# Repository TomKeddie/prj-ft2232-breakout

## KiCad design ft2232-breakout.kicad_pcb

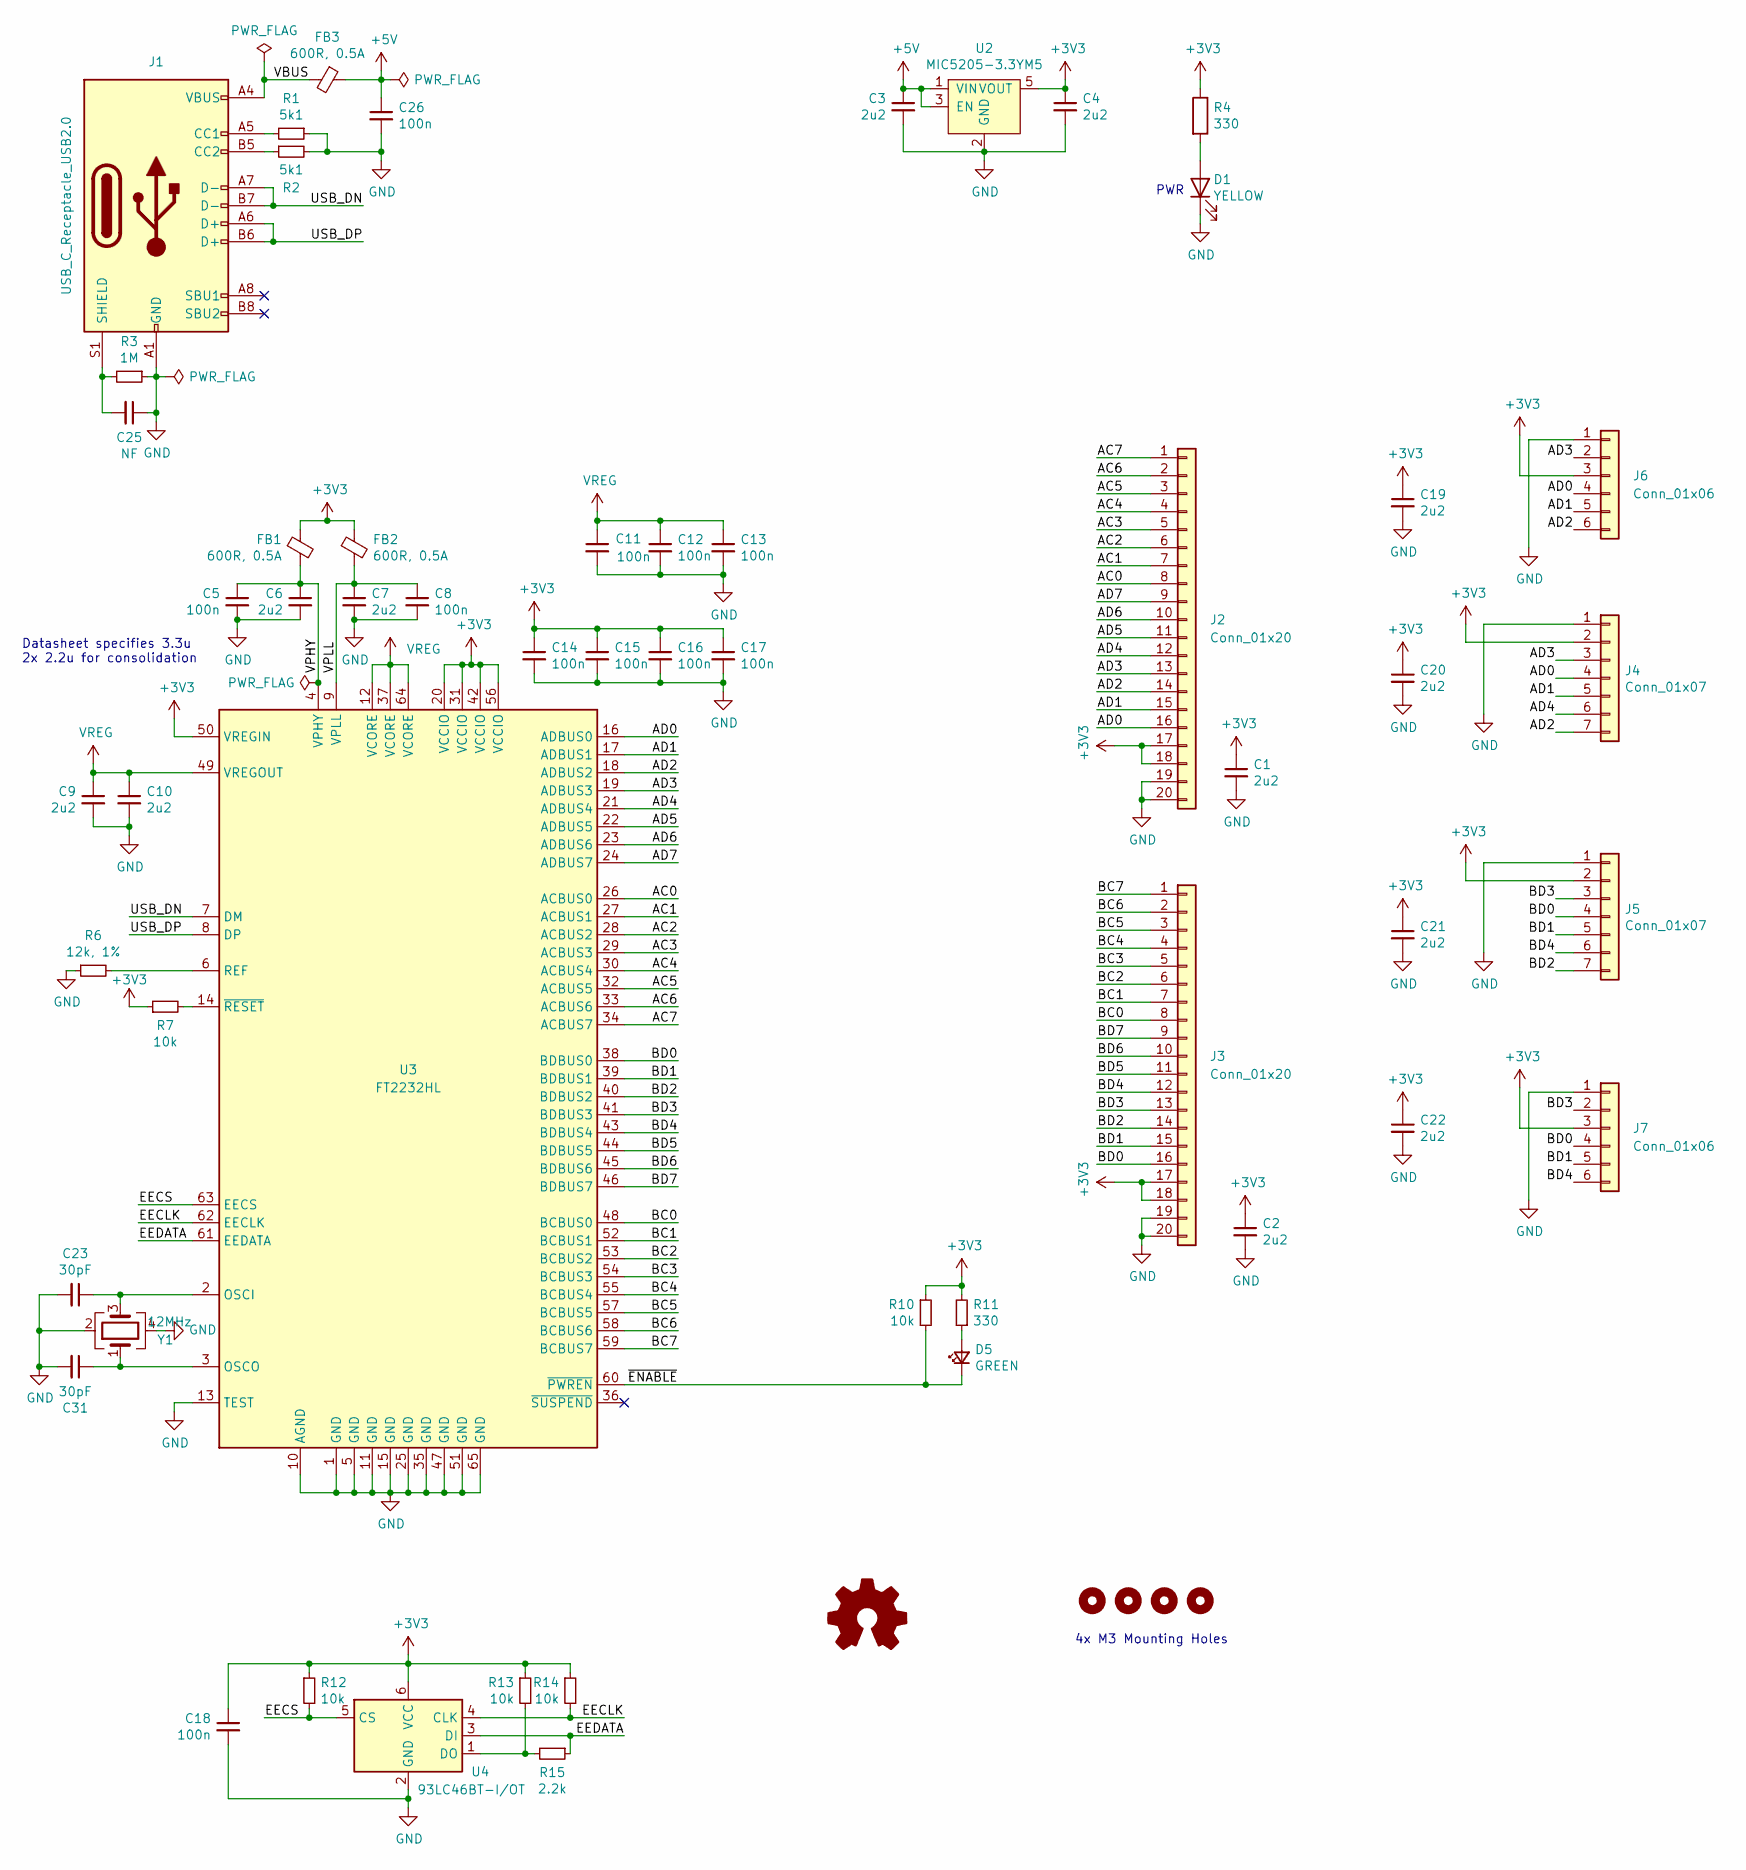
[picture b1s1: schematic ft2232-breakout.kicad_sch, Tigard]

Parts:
C1, C2, C3, C4, C6, C7, C9, C10, C19, C20, C21, C22: 2u2; C_0805_2012Metric; LCSC C307419
C5, C8, C11, C12, C13, C14, C15, C16, C17, C18, C26: 100n; C_0805_2012Metric; LCSC C100072
C23, C31: 30pF; C_0805_2012Metric; LCSC C159804
C25: NF; C_0805_2012Metric
D1: YELLOW; LED_0805_2012Metric; LCSC C160477
D5: GREEN; LED_0805_2012Metric; LCSC C12065
FB1, FB2, FB3: 600R, 0.5A; L_0805_2012Metric; LCSC C76886
H1, H2, H3, H4: MountingHole; MountingHole_3.2mm_M3_ISO7380
J1: USB_C_Receptacle_USB2.0; USB_C_Receptacle_HRO_TYPE-C-31-M-12; LCSC C165948
J2, J3: Conn_01x20; PinHeader_1x20_P2.54mm_Horizontal
J4, J5: Conn_01x07; PinHeader_1x07_P2.54mm_Horizontal
J6, J7: Conn_01x06; PinHeader_1x06_P2.54mm_Horizontal
LOGO1: Logo_Open_Hardware_Small; OSHW-Symbol_4.4x4mm_SilkScreen
R1, R2: 5k1; L_0805_2012Metric; LCSC C25941
R3: 1M; L_0805_2012Metric; LCSC C26087
R4, R11: 330; L_0805_2012Metric; LCSC C25104
R6: 12k, 1%; L_0805_2012Metric; LCSC C25752
R7, R10, R12, R13, R14: 10k; L_0805_2012Metric; LCSC C301923
R15: 2.2k; L_0805_2012Metric; LCSC C25879
U2: MIC5205-3.3YM5; SOT-23-5_RoundRect; LCSC C150742
U3: FT2232HL; LQFP-64_10x10mm_P0.5mm; LCSC C193662
U4: 93LC46BT-I/OT; SOT-23-6_RoundRect; LCSC C190271
Y1: 12MHz; Crystal_SMD_3225-4Pin_3.2x2.5mm_RoundRect; LCSC C9002

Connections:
+3V3: C1.1, C2.1, C4.1, C14.1, C15.1, C16.1, C17.1, C18.1, C19.1, C20.1, C21.1, C22.1, FB1.1, FB2.1, J2.17, J2.18, J3.17, J3.18, J4.2, J5.2, J6.3, J7.3, R4.1, R7.1, R10.1, R11.2, R12.1, R13.1, R14.1, U2.5 (VOUT), U3.20 (VCCIO), U3.31 (VCCIO), U3.42 (VCCIO), U3.50 (VREGIN), U3.56 (VCCIO), U4.6 (VCC)
+5V: C3.1, C26.1, FB3.1, U2.1 (VIN), U2.3 (EN)
/AC0: J2.8, U3.26 (ACBUS0)
/AC1: J2.7, U3.27 (ACBUS1)
/AC2: J2.6, U3.28 (ACBUS2)
/AC3: J2.5, U3.29 (ACBUS3)
/AC4: J2.4, U3.30 (ACBUS4)
/AC5: J2.3, U3.32 (ACBUS5)
/AC6: J2.2, U3.33 (ACBUS6)
/AC7: J2.1, U3.34 (ACBUS7)
/AD0: J2.16, J4.4, J6.4, U3.16 (ADBUS0)
/AD1: J2.15, J4.5, J6.5, U3.17 (ADBUS1)
/AD2: J2.14, J4.7, J6.6, U3.18 (ADBUS2)
/AD3: J2.13, J4.3, J6.2, U3.19 (ADBUS3)
/AD4: J2.12, J4.6, U3.21 (ADBUS4)
/AD5: J2.11, U3.22 (ADBUS5)
/AD6: J2.10, U3.23 (ADBUS6)
/AD7: J2.9, U3.24 (ADBUS7)
/BC0: J3.8, U3.48 (BCBUS0)
/BC1: J3.7, U3.52 (BCBUS1)
/BC2: J3.6, U3.53 (BCBUS2)
/BC3: J3.5, U3.54 (BCBUS3)
/BC4: J3.4, U3.55 (BCBUS4)
/BC5: J3.3, U3.57 (BCBUS5)
/BC6: J3.2, U3.58 (BCBUS6)
/BC7: J3.1, U3.59 (BCBUS7)
/BD0: J3.16, J5.4, J7.4, U3.38 (BDBUS0)
/BD1: J3.15, J5.5, J7.5, U3.39 (BDBUS1)
/BD2: J3.14, J5.7, U3.40 (BDBUS2)
/BD3: J3.13, J5.3, J7.2, U3.41 (BDBUS3)
/BD4: J3.12, J5.6, J7.6, U3.43 (BDBUS4)
/BD5: J3.11, U3.44 (BDBUS5)
/BD6: J3.10, U3.45 (BDBUS6)
/BD7: J3.9, U3.46 (BDBUS7)
/EECLK: R14.2, U3.62 (EECLK), U4.4 (CLK)
/EECS: R12.2, U3.63 (EECS), U4.5 (CS)
/EEDATA: R15.1, U3.61 (EEDATA), U4.3 (DI)
/USB_DN: J1.A7 (D-), J1.B7 (D-), U3.7 (DM)
/USB_DP: J1.A6 (D+), J1.B6 (D+), U3.8 (DP)
/VBUS: FB3.2, J1.A4 (VBUS), J1.A9 (VBUS), J1.B4 (VBUS), J1.B9 (VBUS)
/VPHY: C5.1, C6.1, FB1.2, U3.4 (VPHY)
/VPLL: C7.1, C8.1, FB2.2, U3.9 (VPLL)
/~ENABLE: D5.1 (K), R10.2, U3.60 (~PWREN)
GND: C1.2, C2.2, C3.2, C4.2, C5.2, C6.2, C7.2, C8.2, C9.2, C10.2, C11.2, C12.2, C13.2, C14.2, C15.2, C16.2, C17.2, C18.2, C19.2, C20.2, C21.2, C22.2, C23.2, C25.1, C26.2, C31.2, D1.1 (K), J1.A1 (GND), J1.A12 (GND), J1.B1 (GND), J1.B12 (GND), J2.19, J2.20, J3.19, J3.20, J4.1, J5.1, J6.1, J7.1, R1.1, R2.2, R3.1, R6.1, U2.2 (GND), U3.1 (GND), U3.5 (GND), U3.10 (AGND), U3.11 (GND), U3.13 (TEST), U3.15 (GND), U3.25 (GND), U3.35 (GND), U3.47 (GND), U3.51 (GND), U3.65 (GND), U4.2 (GND), Y1.2, Y1.4
unnamed: C23.1, U3.2 (OSCI), Y1.3
unnamed: C25.2, J1.S1 (SHIELD), R3.2
unnamed: C31.1, U3.3 (OSCO), Y1.1
unnamed: D1.2 (A), R4.2
unnamed: D5.2 (A), R11.1
unnamed: J1.A5 (CC1), R1.2
unnamed: J1.B5 (CC2), R2.1
unnamed: R6.2, U3.6 (REF)
unnamed: R7.2, U3.14 (~RESET)
unnamed: R13.2, R15.2, U4.1 (DO)
VREG: C9.1, C10.1, C11.1, C12.1, C13.1, U3.12 (VCORE), U3.37 (VCORE), U3.49 (VREGOUT), U3.64 (VCORE)

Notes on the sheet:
PWR
Datasheet specifies 3.3u 2x 2.2u for consolidation
4x M3 Mounting Holes

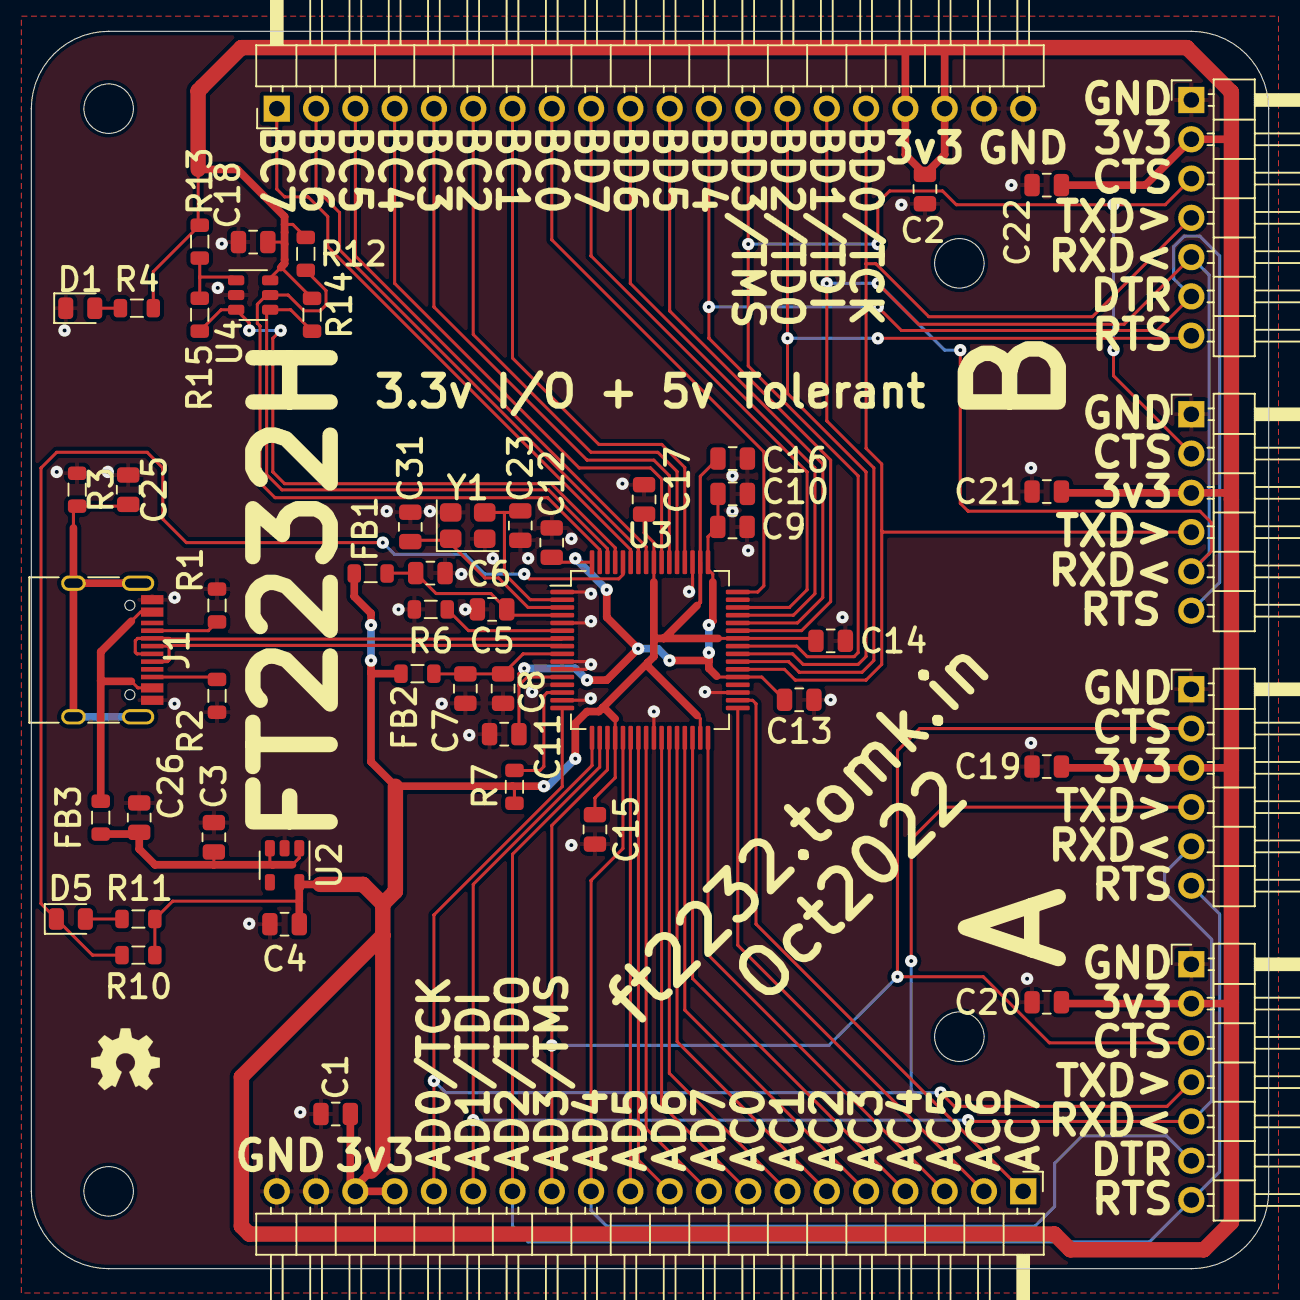
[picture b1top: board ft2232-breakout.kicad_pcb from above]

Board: 2 copper layers, 80.0 x 80.0 mm, 59 parts (0 on the bottom side), 55 nets.

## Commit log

2022-10-12 As sent to jlcpcb 2022-10-12a
2022-10-12 remove dupe licence
2022-12-15 Oct2022 as manufactured

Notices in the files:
ft2232-breakout.kicad_sch:
Copyright 2020 Franklin Harding
Licensed under CC-BY-SA 4.0
